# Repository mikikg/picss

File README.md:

# PIC Soft Start

230VAC 2kVA Soft-start circuit with PIC16F15313 microcontroller.

This repository includes:
* Mplab X project for PIC firmware with source files and compiled HEX
* KiCAD project files for schematic and PCB

# Specification

* Input voltage: 230VAC
* Input frequency: 50Hz
* Max power output: 2kVA
* Phase angle control: 0° - 180° (100% - 0% power)
* Slope time: 0.1sec - 10sec

# Warning

This circuit operates on the mains high voltage line, do not touch any part of this device!

Please note that additional mains FUSE IS REQUIRED.

# More info

For more information please visit the project forum thread at https://forum.yu3ma.net/thread-1807-newpost.html

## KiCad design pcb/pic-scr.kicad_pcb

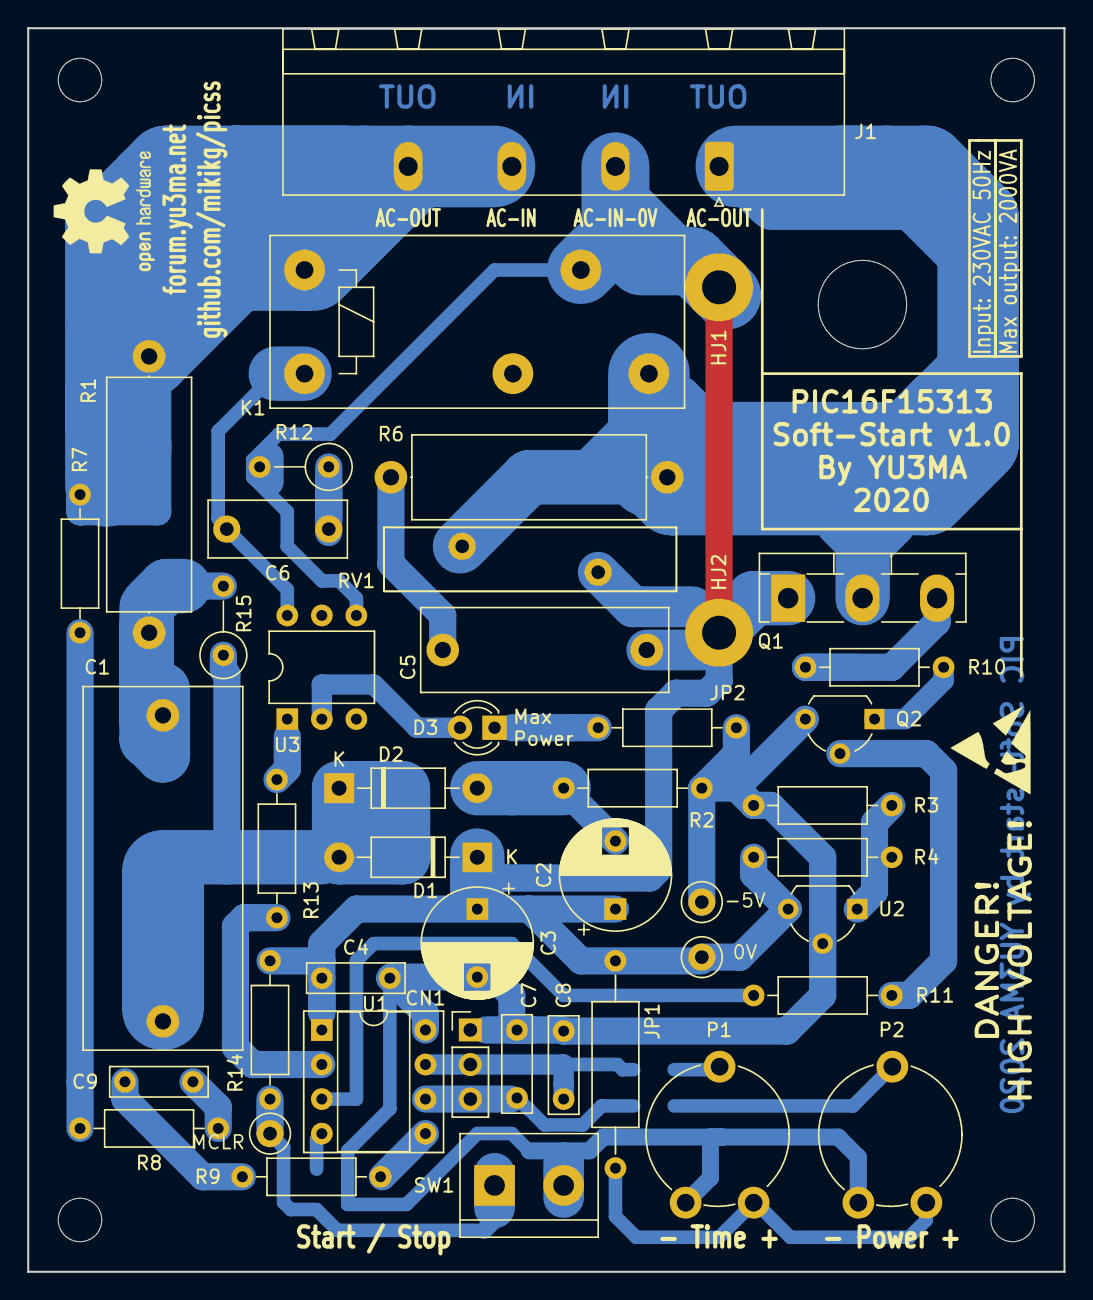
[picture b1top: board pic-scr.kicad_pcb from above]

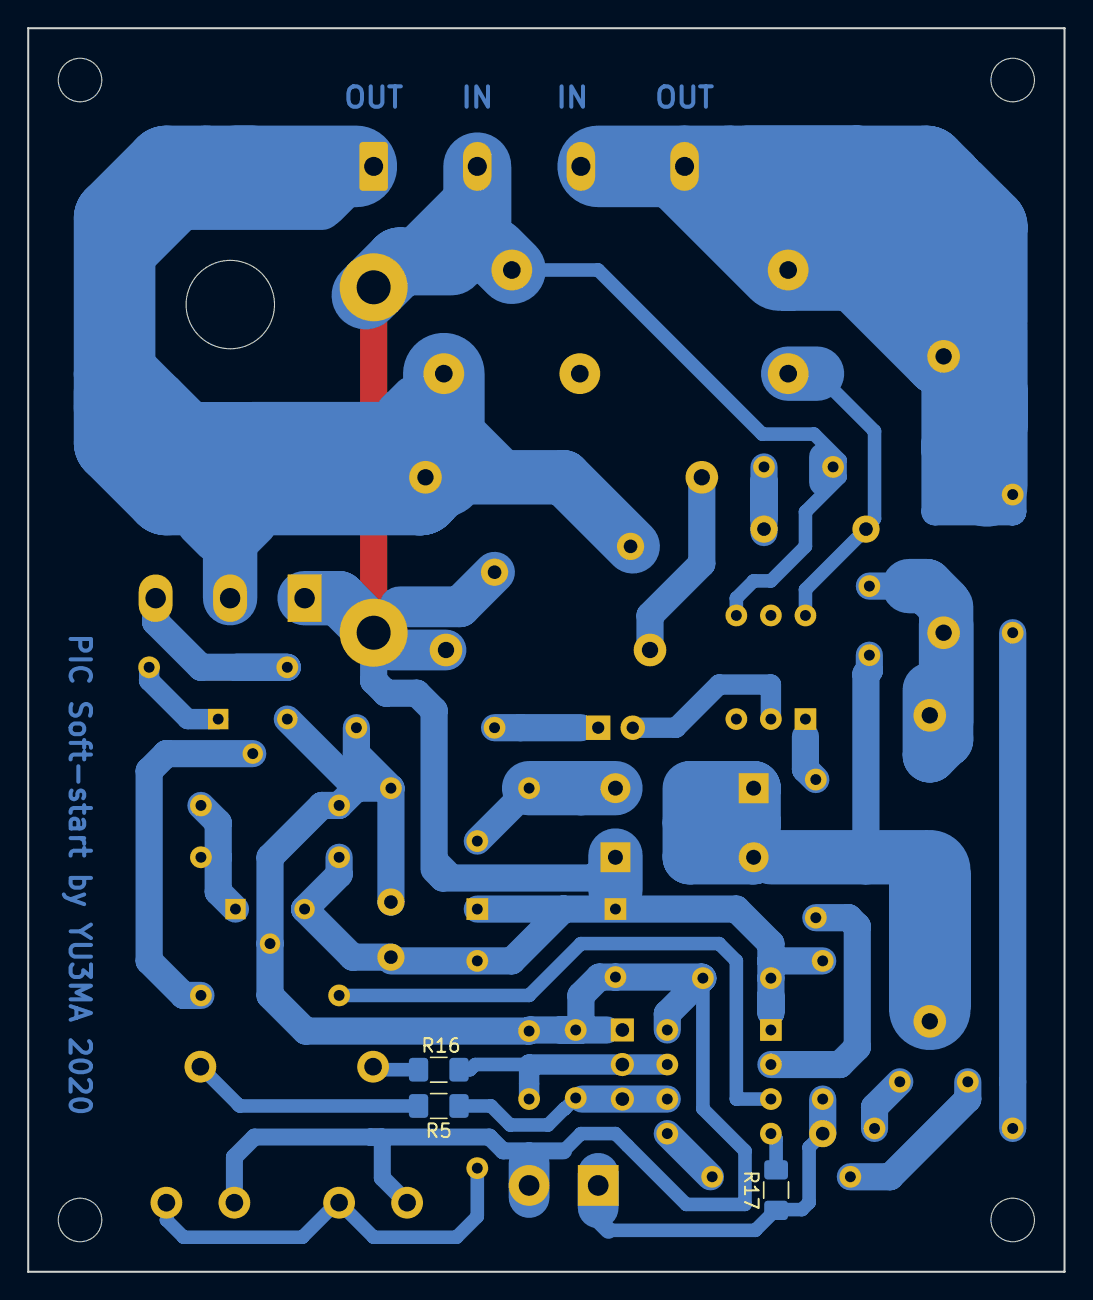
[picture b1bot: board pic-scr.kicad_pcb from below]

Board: 2 copper layers, 76.2 x 91.4 mm, 53 parts (3 on the bottom side), 30 nets.

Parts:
C1: 1uF/630V; C_Rect_L26.5mm_W11.5mm_P22.50mm_MKS4
C2: 100uF/35V; CP_Radial_D8.0mm_P5.00mm
C3: 100uF/25V; CP_Radial_D8.0mm_P5.00mm
C4, C7, C8: 100nF; C_Rect_L7.0mm_W2.0mm_P5.00mm
C5: 100n/630; C_Rect_L18.0mm_W6.0mm_P15.00mm_FKS3_FKP3
C6: 10nF/250V; C_Rect_L10.0mm_W4.0mm_P7.50mm_MKS4
C9: 100nF/63V; C_Rect_L7.0mm_W2.0mm_P5.00mm
CN1: USART; PinHeader_1x03_P2.54mm_Vertical
D1: 6v8/1.2W; D_DO-41_SOD81_P10.16mm_Horizontal
D2: 1N4001; D_DO-41_SOD81_P10.16mm_Horizontal
D3: LED; LED_D3.0mm
H1, H2, H3, H4: MountingHole_Pad; MountingHole_3.2mm_M3
H5: MountingHole_Pad; MountingHole_6.5mm
HJ1, HJ2: MountingHole_Pad; MountingHole_2.5mm_Pad
J1: Conn_01x02_Male; PhoenixContact_GMSTB_2,5_4-GF-7,62_1x04_P7.62mm_Horizontal_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
J2: -5V; TestPoint_Loop_D2.50mm_Drill1.0mm
J3: 0V; TestPoint_Loop_D2.50mm_Drill1.0mm
J4: MCLR; TestPoint_Loop_D2.50mm_Drill1.0mm
JP1: Jumper; R_Axial_DIN0309_L9.0mm_D3.2mm_P15.24mm_Horizontal
JP2: Jumper; R_Axial_DIN0207_L6.3mm_D2.5mm_P10.16mm_Horizontal
K1: RELAY; Relay_SPDT_Schrack-RP-II-1-FormC_RM5mm
P1, P2: 10K; Potentiometer_Piher_PT-10-V10_Vertical
Q1: BTA41-600B; TO-218-3_Vertical
Q2: BC548; TO-92L_Wide
R1: 220R/2W; R_Axial_DIN0617_L17.0mm_D6.0mm_P20.32mm_Horizontal
R2: 27R-33R; R_Axial_DIN0207_L6.3mm_D2.5mm_P10.16mm_Horizontal
R3, R4: 10K; R_Axial_DIN0207_L6.3mm_D2.5mm_P10.16mm_Horizontal
R5, R16, R17: 470R; R_1206_3216Metric_Pad1.42x1.75mm_HandSolder
R6: 150/2W; R_Axial_DIN0617_L17.0mm_D6.0mm_P20.32mm_Horizontal
R7, R8: 270K/0.25W; R_Axial_DIN0207_L6.3mm_D2.5mm_P10.16mm_Horizontal
R9: 220K/0.25W; R_Axial_DIN0207_L6.3mm_D2.5mm_P10.16mm_Horizontal
R10: 33R; R_Axial_DIN0207_L6.3mm_D2.5mm_P10.16mm_Horizontal
R11, R14: 4K7; R_Axial_DIN0207_L6.3mm_D2.5mm_P10.16mm_Horizontal
R12: 360R; R_Axial_DIN0309_L9.0mm_D3.2mm_P5.08mm_Vertical
R13: 470R; R_Axial_DIN0207_L6.3mm_D2.5mm_P10.16mm_Horizontal
R15: 3M/0.25W; R_Axial_DIN0309_L9.0mm_D3.2mm_P5.08mm_Vertical
RV1: JVR20N681K; RV_Disc_D21.5mm_W4.7mm_P10mm
SW1: Start/Stop; TerminalBlock_bornier-2_P5.08mm
U1: PIC16F15313E/P; DIP-8_W7.62mm_Socket
U2: TL431LP; TO-92L_Wide
U3: MOC3043M; DIP-6_W7.62mm

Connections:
-5V: C3.2, C4.2, C7.2, C8.2, CN1.1, J2.1, JP2.2, P1.3, P2.3, Q2.3, R2.1, R3.1, SW1.2, U1.8, U2.2
/0V: C2.1, C3.1, C4.1, C5.2, D1.1, HJ1.1, HJ2.1, J1.2, J3.1, JP1.1, K1.11, Q1.1, R4.2, R12.2, R14.1, RV1.2, U1.1, U2.3, U3.4
unnamed: C1.1, D1.2, D2.1, R15.1
unnamed: C1.2, R1.1, R15.2
unnamed: C2.2, D2.2, R2.2
unnamed: C5.1, R6.2
unnamed: C6.1, R12.1
unnamed: C6.2, K1.A2, U3.6
unnamed: C7.1, CN1.3, R5.1, U1.6
unnamed: C8.1, CN1.2, R16.1, U1.7
unnamed: C9.1, R9.1
unnamed: C9.2, R8.2
unnamed: D3.1, JP2.1
unnamed: D3.2, U3.2
unnamed: J1.1, K1.14, Q1.2, R6.1, RV1.1
unnamed: J1.3, J1.4, K1.A1, R1.2, R7.1
unnamed: J4.1, R14.2, R17.1, SW1.1
unnamed: JP1.2, P1.1, P2.1
unnamed: P1.2, R16.2
unnamed: P2.2, R5.2
unnamed: Q1.3, R10.1
unnamed: Q2.1, R10.2
unnamed: Q2.2, R11.2
unnamed: R3.2, R4.1, U2.1
unnamed: R7.2, R8.1
unnamed: R9.2, U1.5
unnamed: R11.1, U1.3
unnamed: R13.1, U1.2
unnamed: R13.2, U3.1
unnamed: R17.2, U1.4

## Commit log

2020-08-11 Initital import
2020-08-11 Added KiCad screenshot
2020-08-11 Updated KiCad screenshot
2020-08-11 Updated documentation PDF
2020-08-11 Added Application Note AN2184
2020-08-14 Updated program logic
2020-08-15 Updated TMR0_ISR code
2020-08-18 Inverted RLY_OUT logic, enlarge triger pulse to 2ms
2020-08-18 Updated shematic and PCB
2020-08-18 Updated schematic in PDF
